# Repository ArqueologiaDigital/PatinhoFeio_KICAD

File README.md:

Para o desenvolvimento desse projeto estou atualmente (Julho de 2025) utilizando o Kicad versão 9.0.2+dfsg-1 instalado a partir do repositório de pacotes do Debian 13.
----

Existe um arquivo patinhofeio.pro na raiz desse repo que referencia os demais sub-projetos de cada placa.

Em JAN/2018 eu encomendei a fabicação das PCBs CDE-3 e CDE-3-debug. Há um relato detalhado em https://forum.fiozera.com.br/t/resgate-historico-do-computador-patinho-feio-usp-1971/58/18

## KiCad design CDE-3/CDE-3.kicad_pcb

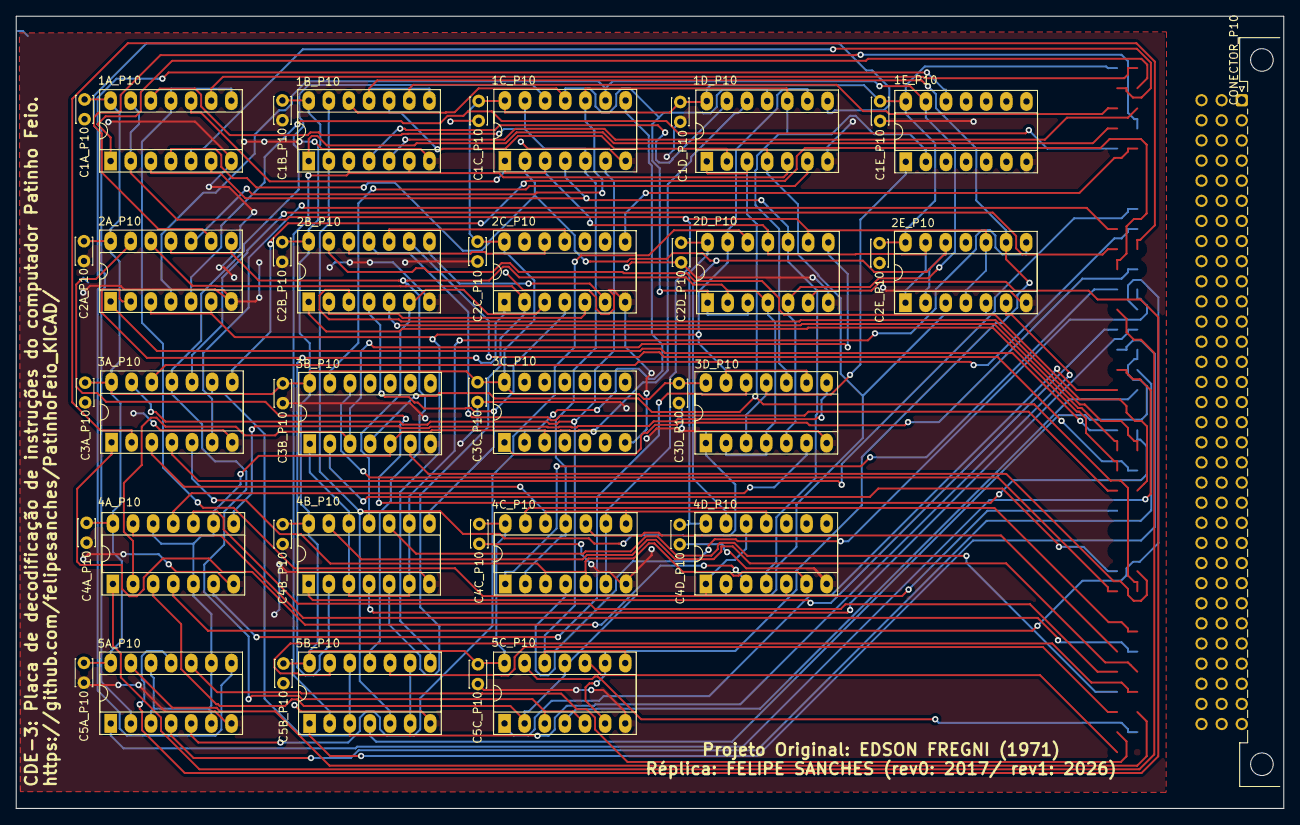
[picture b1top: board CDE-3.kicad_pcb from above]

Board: 2 copper layers, 160.0 x 100.0 mm, 43 parts (0 on the bottom side), 96 nets.

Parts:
1A_P10, 1B_P10, 2A_P10, 2B_P10, 3A_P10, 3B_P10: 74HC04; DIP-14_W7.62mm_Socket_LongPads
1C_P10, 1D_P10, 1E_P10, 2D_P10, 3D_P10: 74LS10; DIP-14_W7.62mm_Socket_LongPads
2C_P10: 74LS30; DIP-14_W7.62mm_Socket_LongPads
2E_P10: 74LS13; DIP-14_W7.62mm_Socket_LongPads
3C_P10, 4A_P10, 4B_P10, 4C_P10, 5A_P10, 5B_P10, 5C_P10: 7402; DIP-14_W7.62mm_Socket_LongPads
4D_P10: 7400; DIP-14_W7.62mm_Socket_LongPads
C1A_P10, C1B_P10, C1C_P10, C1D_P10, C1E_P10, C2A_P10, C2B_P10, C2C_P10, C2D_P10, C2E_P10, C3A_P10, C3B_P10, C3C_P10, C3D_P10, C4A_P10, C4B_P10, C4C_P10, C4D_P10, C5A_P10, C5B_P10, C5C_P10: 0.1uF; C_Disc_D3.4mm_W2.1mm_P2.50mm
CONECTOR_P10: CONN_35X2; DIN41612_C_3x32_Male_Horizontal_THT

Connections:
(+)RI_0: 1A_P10.10, 1C_P10.1, 1C_P10.3, 2D_P10.11, 2E_P10.1, 2E_P10.13
(+)RI_1: 1A_P10.4, 1C_P10.2, 2E_P10.2, 2E_P10.12, 4D_P10.13
(+)RI_2: 1A_P10.12, 1C_P10.5, 1C_P10.13, 4C_P10.2, 4C_P10.11
(+)RI_3: 1B_P10.10, 1D_P10.2, 1D_P10.4, 2E_P10.5, 4A_P10.3, 4D_P10.2, 5C_P10.2, 5C_P10.11
(+)RI_4: 1B_P10.4, 1D_P10.13
(+)RI_5: 1B_P10.12, 1C_P10.11, 1D_P10.11, 2D_P10.1, 2D_P10.3
(+)RI_6: 1C_P10.10, 1D_P10.10, 1E_P10.2, 2A_P10.10, 3D_P10.10
(+)RI_7: 1C_P10.9, 1E_P10.13, 2A_P10.4, 2D_P10.5, 3D_P10.5
+(CAC+SOM): 3A_P10.4, CONECTOR_P10.a20
+(PAN+PAZ): 3A_P10.10, CONECTOR_P10.a16
+(PLI+ARA): 3A_P10.6, CONECTOR_P10.a18
+(SUS+PUG): 3A_P10.12, CONECTOR_P10.a17
+ARA: 4C_P10.4, CONECTOR_P10.a8
+CAC: 4C_P10.13, CONECTOR_P10.b12
+ESP-D: 5A_P10.4, CONECTOR_P10.a32
+IME: 3A_P10.8, CONECTOR_P10.a29
+IMEADD: 5B_P10.1, CONECTOR_P10.c13
+IMENAND: 5B_P10.4, CONECTOR_P10.a7
+IMEXOR: 5B_P10.13, CONECTOR_P10.c7
+INDICE: 3A_P10.2, CONECTOR_P10.a15
+INI: 4A_P10.10, CONECTOR_P10.c10
+MIC: 1D_P10.1, 1D_P10.3, 3B_P10.4, CONECTOR_P10.c4
+MICG1: 4A_P10.1, CONECTOR_P10.a11
+MICG2A: 3B_P10.12, CONECTOR_P10.b26
+MICG2B: 3B_P10.6, CONECTOR_P10.a19
+PAN: 5C_P10.13, CONECTOR_P10.c21
+PAR-D: 5A_P10.13, CONECTOR_P10.b17
+PAZ: 5C_P10.10, CONECTOR_P10.b11
+PER: 5A_P10.1, CONECTOR_P10.c31
+PLI: 4C_P10.1, CONECTOR_P10.b31
+PUG: 5C_P10.4, CONECTOR_P10.a13
+PUL: 4A_P10.4, CONECTOR_P10.a10
+RD_0: 2A_P10.1, CONECTOR_P10.a9
+RD_1: 2A_P10.13, CONECTOR_P10.b14
+RD_2: 2B_P10.5, CONECTOR_P10.a4
+RD_3: 2B_P10.3, CONECTOR_P10.a3
+RD_4: 2B_P10.1, CONECTOR_P10.b25
+RD_5: 2B_P10.9, CONECTOR_P10.c5
+RD_6: 2B_P10.11, CONECTOR_P10.b10
+RD_7: 2B_P10.13, CONECTOR_P10.b6
+RESERVADO: 3C_P10.1, CONECTOR_P10.a28
+RI_0: 1A_P10.9, CONECTOR_P10.a2
+RI_1: 1A_P10.5, CONECTOR_P10.b1
+RI_2: 1A_P10.1, CONECTOR_P10.b2
+RI_3: 1B_P10.9, CONECTOR_P10.c1
+RI_4: 1B_P10.5, CONECTOR_P10.c2
+RI_5: 1B_P10.1, CONECTOR_P10.a25
+RI_6: 2A_P10.9, CONECTOR_P10.b19
+RI_7: 2A_P10.5, CONECTOR_P10.b16
+SAE: 3B_P10.2, CONECTOR_P10.a31
+SAEDE: 4B_P10.4, CONECTOR_P10.b28
+SAEDS: 4B_P10.1, CONECTOR_P10.b32
+SAEFU: 4B_P10.10, CONECTOR_P10.c8
+SAESA: 4B_P10.13, CONECTOR_P10.c9
+SHIFT: 5B_P10.10, CONECTOR_P10.c14
+SOM: 4C_P10.10, CONECTOR_P10.c12
+SUS: 5C_P10.1, CONECTOR_P10.b20
+TRI: 5A_P10.10, CONECTOR_P10.b18
+TRO: 4A_P10.13, CONECTOR_P10.c11
-RDZ: 2C_P10.8, CONECTOR_P10.b15
-RD_0: 2A_P10.2, 2C_P10.1, 4B_P10.2
-RD_1: 2A_P10.12, 2C_P10.2, 4B_P10.5
-RD_2: 2B_P10.6, 2C_P10.3, 4B_P10.11
-RD_3: 2B_P10.4, 2C_P10.4, 4B_P10.8
-RD_4: 2B_P10.2, 2C_P10.5
-RD_5: 2B_P10.8, 2C_P10.6
-RD_6: 2B_P10.10, 2C_P10.11
-RD_7: 2B_P10.12, 2C_P10.12
-RI_0: 1A_P10.8, 1A_P10.11, 4D_P10.1, 4D_P10.5, 4D_P10.12, CONECTOR_P10.b13
-RI_1: 1A_P10.3, 1A_P10.6, 1C_P10.4, 2D_P10.10, 4D_P10.4
-RI_2: 1A_P10.2, 1A_P10.13, 2D_P10.9, 2E_P10.4, 2E_P10.10, 4C_P10.6, 4C_P10.9
-RI_3: 1B_P10.8, 1B_P10.11, 2E_P10.9, 5C_P10.6, 5C_P10.9
-RI_4: 1B_P10.3, 1B_P10.6, 1D_P10.5, 5B_P10.2
-RI_5: 1B_P10.2, 1B_P10.13, 1E_P10.1, 3D_P10.1, 3D_P10.3, 3D_P10.11, 5B_P10.5
-RI_6: 2A_P10.8, 2A_P10.11, 2D_P10.2, 2D_P10.4, 3D_P10.2, 3D_P10.4, 5B_P10.11
-RI_7: 1D_P10.9, 2A_P10.3, 2A_P10.6, 2D_P10.13, 3D_P10.9, 3D_P10.13, 5B_P10.8
GND: 1A_P10.7, 1B_P10.7, 1C_P10.7, 1D_P10.7, 1E_P10.7, 2A_P10.7, 2B_P10.7, 2C_P10.7, 2D_P10.7, 2E_P10.7, 3A_P10.7, 3B_P10.7, 3C_P10.7, 3D_P10.7, 4A_P10.7, 4B_P10.7, 4C_P10.7, 4D_P10.7, 5A_P10.7, 5B_P10.7, 5C_P10.7, C1A_P10.2, C1B_P10.2, C1C_P10.2, C1D_P10.2, C1E_P10.2, C2A_P10.2, C2B_P10.2, C2C_P10.2, C2D_P10.2, C2E_P10.2, C3A_P10.2, C3B_P10.2, C3C_P10.2, C3D_P10.2, C4A_P10.2, C4B_P10.2, C4C_P10.2, C4D_P10.2, C5A_P10.2, C5B_P10.2, C5C_P10.2, CONECTOR_P10.c22
unnamed: 1C_P10.6, 3A_P10.13, 5C_P10.8, 5C_P10.12
unnamed: 1C_P10.8, 3C_P10.2
unnamed: 1C_P10.12, 3A_P10.11, 5C_P10.3, 5C_P10.5
unnamed: 1D_P10.6, 3B_P10.13
unnamed: 1D_P10.8, 5A_P10.8
unnamed: 1D_P10.12, 3B_P10.5, 3C_P10.3, 4A_P10.5, 4A_P10.9, 4A_P10.12, 5A_P10.3, 5A_P10.6, 5A_P10.9, 5A_P10.12
unnamed: 1E_P10.12, 5A_P10.2
unnamed: 2D_P10.6, 5A_P10.11
unnamed: 2D_P10.8, 3B_P10.3, 4A_P10.2
unnamed: 2D_P10.12, 5A_P10.5
unnamed: 2E_P10.6, 3A_P10.9, 5B_P10.3, 5B_P10.6, 5B_P10.9, 5B_P10.12
unnamed: 2E_P10.8, 3B_P10.1, 4B_P10.3, 4B_P10.6, 4B_P10.9, 4B_P10.12
unnamed: 3A_P10.1, 4D_P10.3
unnamed: 3A_P10.3, 4C_P10.8, 4C_P10.12, 4D_P10.11
unnamed: 3A_P10.5, 4C_P10.3, 4C_P10.5, 4D_P10.6
unnamed: 3D_P10.6, 4A_P10.11
unnamed: 3D_P10.8, 4A_P10.8
unnamed: 3D_P10.12, 4A_P10.6
VCC: 1A_P10.14, 1B_P10.14, 1C_P10.14, 1D_P10.14, 1E_P10.14, 2A_P10.14, 2B_P10.14, 2C_P10.14, 2D_P10.14, 2E_P10.14, 3A_P10.14, 3B_P10.14, 3C_P10.14, 3D_P10.14, 4A_P10.14, 4B_P10.14, 4C_P10.14, 4D_P10.14, 5A_P10.14, 5B_P10.14, 5C_P10.14, C1A_P10.1, C1B_P10.1, C1C_P10.1, C1D_P10.1, C1E_P10.1, C2A_P10.1, C2B_P10.1, C2C_P10.1, C2D_P10.1, C2E_P10.1, C3A_P10.1, C3B_P10.1, C3C_P10.1, C3D_P10.1, C4A_P10.1, C4B_P10.1, C4C_P10.1, C4D_P10.1, C5A_P10.1, C5B_P10.1, C5C_P10.1, CONECTOR_P10.a1

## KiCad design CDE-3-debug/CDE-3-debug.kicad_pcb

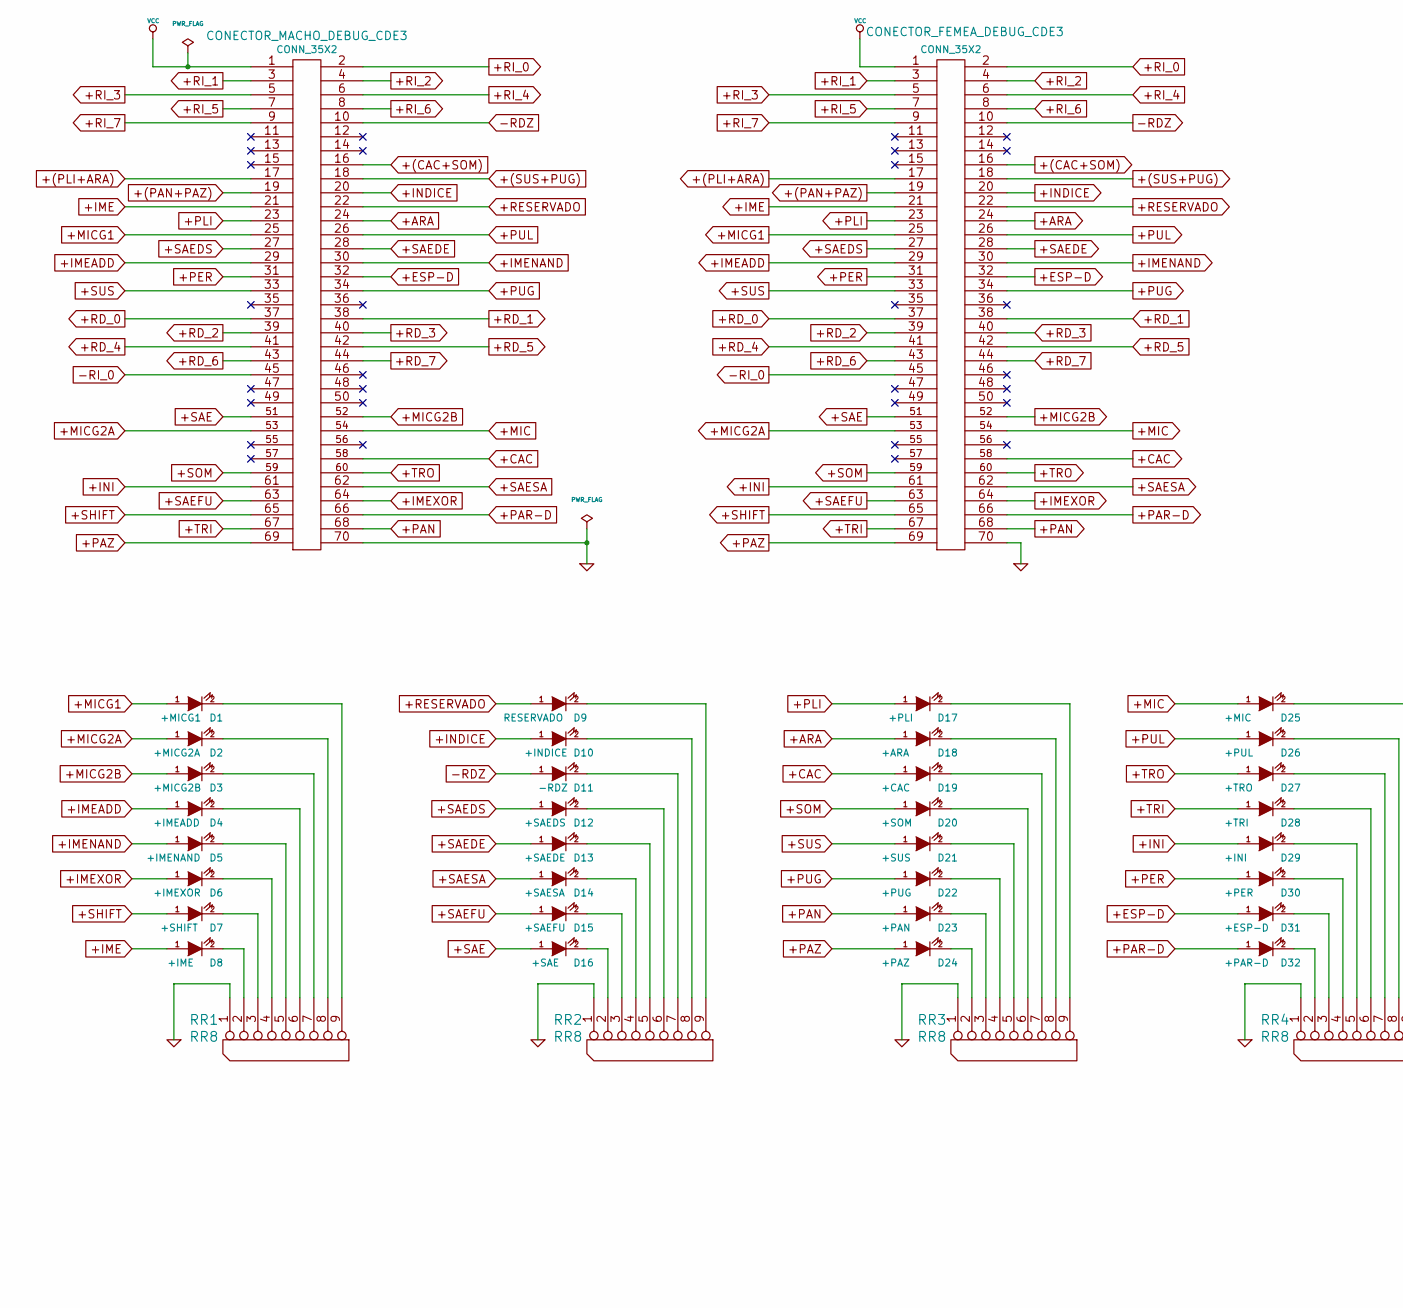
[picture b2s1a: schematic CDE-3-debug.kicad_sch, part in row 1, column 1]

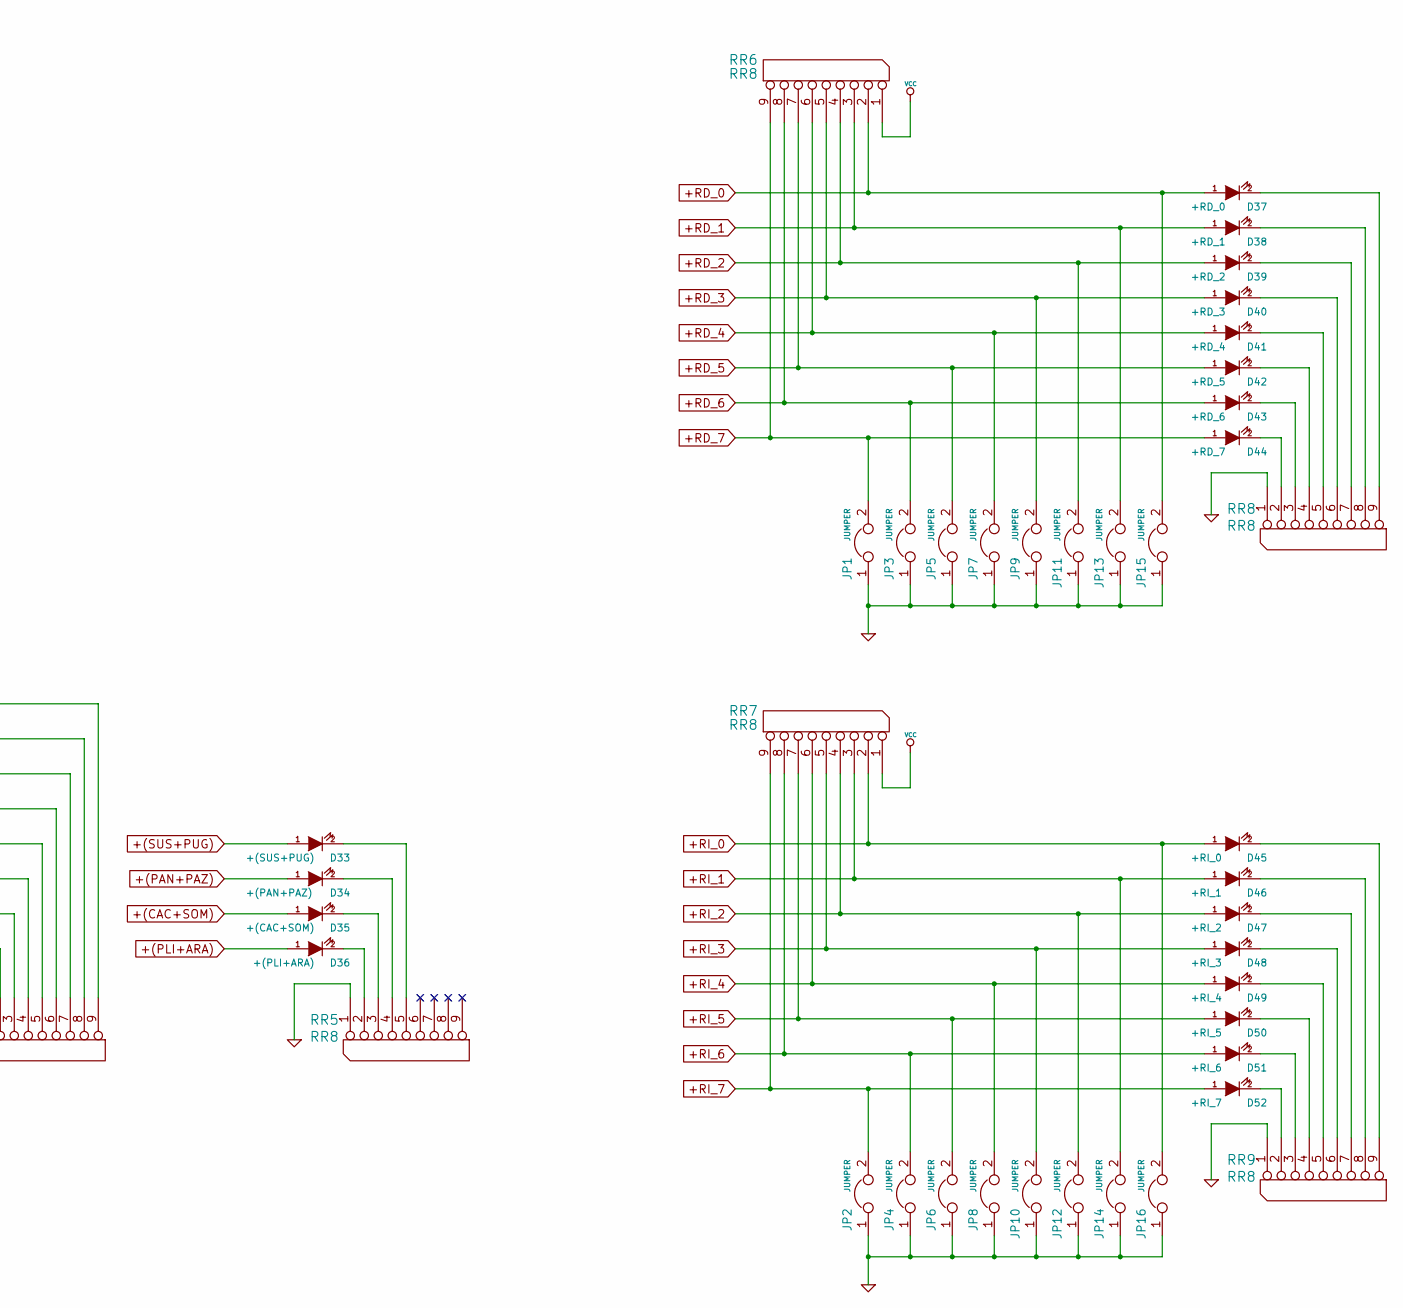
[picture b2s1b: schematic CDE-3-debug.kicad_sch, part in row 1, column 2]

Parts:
CONECTOR_FEMEA_DEBUG_CDE3: CONN_35X2; Pin_Header_Angled_2x35_Pitch2.54mm
CONECTOR_MACHO_DEBUG_CDE3: CONN_35X2; Pin_Header_Angled_2x35_Pitch2.54mm
D1: +MICG1; LED_D3.0mm
D2: +MICG2A; LED_D3.0mm
D3: +MICG2B; LED_D3.0mm
D4: +IMEADD; LED_D3.0mm
D5: +IMENAND; LED_D3.0mm
D6: +IMEXOR; LED_D3.0mm
D7: +SHIFT; LED_D3.0mm
D8: +IME; LED_D3.0mm
D9: RESERVADO; LED_D3.0mm
D10: +INDICE; LED_D3.0mm
D11: -RDZ; LED_D3.0mm
D12: +SAEDS; LED_D3.0mm
D13: +SAEDE; LED_D3.0mm
D14: +SAESA; LED_D3.0mm
D15: +SAEFU; LED_D3.0mm
D16: +SAE; LED_D3.0mm
D17: +PLI; LED_D3.0mm
D18: +ARA; LED_D3.0mm
D19: +CAC; LED_D3.0mm
D20: +SOM; LED_D3.0mm
D21: +SUS; LED_D3.0mm
D22: +PUG; LED_D3.0mm
D23: +PAN; LED_D3.0mm
D24: +PAZ; LED_D3.0mm
D25: +MIC; LED_D3.0mm
D26: +PUL; LED_D3.0mm
D27: +TRO; LED_D3.0mm
D28: +TRI; LED_D3.0mm
D29: +INI; LED_D3.0mm
D30: +PER; LED_D3.0mm
D31: +ESP-D; LED_D3.0mm
D32: +PAR-D; LED_D3.0mm
D33: +(SUS+PUG); LED_D3.0mm
D34: +(PAN+PAZ); LED_D3.0mm
D35: +(CAC+SOM); LED_D3.0mm
D36: +(PLI+ARA); LED_D3.0mm
D37: +RD_0; LED_D3.0mm
D38: +RD_1; LED_D3.0mm
D39: +RD_2; LED_D3.0mm
D40: +RD_3; LED_D3.0mm
D41: +RD_4; LED_D3.0mm
D42: +RD_5; LED_D3.0mm
D43: +RD_6; LED_D3.0mm
D44: +RD_7; LED_D3.0mm
D45: +RI_0; LED_D3.0mm
D46: +RI_1; LED_D3.0mm
D47: +RI_2; LED_D3.0mm
D48: +RI_3; LED_D3.0mm
D49: +RI_4; LED_D3.0mm
D50: +RI_5; LED_D3.0mm
D51: +RI_6; LED_D3.0mm
D52: +RI_7; LED_D3.0mm
JP1, JP2, JP3, JP4, JP5, JP6, JP7, JP8, JP9, JP10, JP11, JP12, JP13, JP14, JP15, JP16: JUMPER; Pin_Header_Straight_1x02_Pitch2.54mm
RR1, RR2, RR3, RR4, RR5, RR6, RR7, RR8, RR9: RR8; R_Array_SIP9

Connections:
+(CAC+SOM): CONECTOR_FEMEA_DEBUG_CDE3.16, CONECTOR_MACHO_DEBUG_CDE3.16, D35.1 (A)
+(PAN+PAZ): CONECTOR_FEMEA_DEBUG_CDE3.19, CONECTOR_MACHO_DEBUG_CDE3.19, D34.1 (A)
+(PLI+ARA): CONECTOR_FEMEA_DEBUG_CDE3.17, CONECTOR_MACHO_DEBUG_CDE3.17, D36.1 (A)
+(SUS+PUG): CONECTOR_FEMEA_DEBUG_CDE3.18, CONECTOR_MACHO_DEBUG_CDE3.18, D33.1 (A)
+ARA: CONECTOR_FEMEA_DEBUG_CDE3.24, CONECTOR_MACHO_DEBUG_CDE3.24, D18.1 (A)
+CAC: CONECTOR_FEMEA_DEBUG_CDE3.58, CONECTOR_MACHO_DEBUG_CDE3.58, D19.1 (A)
+ESP-D: CONECTOR_FEMEA_DEBUG_CDE3.32, CONECTOR_MACHO_DEBUG_CDE3.32, D31.1 (A)
+IME: CONECTOR_FEMEA_DEBUG_CDE3.21, CONECTOR_MACHO_DEBUG_CDE3.21, D8.1 (A)
+IMEADD: CONECTOR_FEMEA_DEBUG_CDE3.29, CONECTOR_MACHO_DEBUG_CDE3.29, D4.1 (A)
+IMENAND: CONECTOR_FEMEA_DEBUG_CDE3.30, CONECTOR_MACHO_DEBUG_CDE3.30, D5.1 (A)
+IMEXOR: CONECTOR_FEMEA_DEBUG_CDE3.64, CONECTOR_MACHO_DEBUG_CDE3.64, D6.1 (A)
+INDICE: CONECTOR_FEMEA_DEBUG_CDE3.20, CONECTOR_MACHO_DEBUG_CDE3.20, D10.1 (A)
+INI: CONECTOR_FEMEA_DEBUG_CDE3.61, CONECTOR_MACHO_DEBUG_CDE3.61, D29.1 (A)
+MIC: CONECTOR_FEMEA_DEBUG_CDE3.54, CONECTOR_MACHO_DEBUG_CDE3.54, D25.1 (A)
+MICG1: CONECTOR_FEMEA_DEBUG_CDE3.25, CONECTOR_MACHO_DEBUG_CDE3.25, D1.1 (A)
+MICG2A: CONECTOR_FEMEA_DEBUG_CDE3.53, CONECTOR_MACHO_DEBUG_CDE3.53, D2.1 (A)
+MICG2B: CONECTOR_FEMEA_DEBUG_CDE3.52, CONECTOR_MACHO_DEBUG_CDE3.52, D3.1 (A)
+PAN: CONECTOR_FEMEA_DEBUG_CDE3.68, CONECTOR_MACHO_DEBUG_CDE3.68, D23.1 (A)
+PAR-D: CONECTOR_FEMEA_DEBUG_CDE3.66, CONECTOR_MACHO_DEBUG_CDE3.66, D32.1 (A)
+PAZ: CONECTOR_FEMEA_DEBUG_CDE3.69, CONECTOR_MACHO_DEBUG_CDE3.69, D24.1 (A)
+PER: CONECTOR_FEMEA_DEBUG_CDE3.31, CONECTOR_MACHO_DEBUG_CDE3.31, D30.1 (A)
+PLI: CONECTOR_FEMEA_DEBUG_CDE3.23, CONECTOR_MACHO_DEBUG_CDE3.23, D17.1 (A)
+PUG: CONECTOR_FEMEA_DEBUG_CDE3.34, CONECTOR_MACHO_DEBUG_CDE3.34, D22.1 (A)
+PUL: CONECTOR_FEMEA_DEBUG_CDE3.26, CONECTOR_MACHO_DEBUG_CDE3.26, D26.1 (A)
+RD_0: CONECTOR_FEMEA_DEBUG_CDE3.37, CONECTOR_MACHO_DEBUG_CDE3.37, D37.1 (A), JP15.2, RR6.2
+RD_1: CONECTOR_FEMEA_DEBUG_CDE3.38, CONECTOR_MACHO_DEBUG_CDE3.38, D38.1 (A), JP13.2, RR6.3
+RD_2: CONECTOR_FEMEA_DEBUG_CDE3.39, CONECTOR_MACHO_DEBUG_CDE3.39, D39.1 (A), JP11.2, RR6.4
+RD_3: CONECTOR_FEMEA_DEBUG_CDE3.40, CONECTOR_MACHO_DEBUG_CDE3.40, D40.1 (A), JP9.2, RR6.5
+RD_4: CONECTOR_FEMEA_DEBUG_CDE3.41, CONECTOR_MACHO_DEBUG_CDE3.41, D41.1 (A), JP7.2, RR6.6
+RD_5: CONECTOR_FEMEA_DEBUG_CDE3.42, CONECTOR_MACHO_DEBUG_CDE3.42, D42.1 (A), JP5.2, RR6.7
+RD_6: CONECTOR_FEMEA_DEBUG_CDE3.43, CONECTOR_MACHO_DEBUG_CDE3.43, D43.1 (A), JP3.2, RR6.8
+RD_7: CONECTOR_FEMEA_DEBUG_CDE3.44, CONECTOR_MACHO_DEBUG_CDE3.44, D44.1 (A), JP1.2, RR6.9
+RESERVADO: CONECTOR_FEMEA_DEBUG_CDE3.22, CONECTOR_MACHO_DEBUG_CDE3.22, D9.1 (A)
+RI_0: CONECTOR_FEMEA_DEBUG_CDE3.2, CONECTOR_MACHO_DEBUG_CDE3.2, D45.1 (A), JP16.2, RR7.2
+RI_1: CONECTOR_FEMEA_DEBUG_CDE3.3, CONECTOR_MACHO_DEBUG_CDE3.3, D46.1 (A), JP14.2, RR7.3
+RI_2: CONECTOR_FEMEA_DEBUG_CDE3.4, CONECTOR_MACHO_DEBUG_CDE3.4, D47.1 (A), JP12.2, RR7.4
+RI_3: CONECTOR_FEMEA_DEBUG_CDE3.5, CONECTOR_MACHO_DEBUG_CDE3.5, D48.1 (A), JP10.2, RR7.5
+RI_4: CONECTOR_FEMEA_DEBUG_CDE3.6, CONECTOR_MACHO_DEBUG_CDE3.6, D49.1 (A), JP8.2, RR7.6
+RI_5: CONECTOR_FEMEA_DEBUG_CDE3.7, CONECTOR_MACHO_DEBUG_CDE3.7, D50.1 (A), JP6.2, RR7.7
+RI_6: CONECTOR_FEMEA_DEBUG_CDE3.8, CONECTOR_MACHO_DEBUG_CDE3.8, D51.1 (A), JP4.2, RR7.8
+RI_7: CONECTOR_FEMEA_DEBUG_CDE3.9, CONECTOR_MACHO_DEBUG_CDE3.9, D52.1 (A), JP2.2, RR7.9
+SAE: CONECTOR_FEMEA_DEBUG_CDE3.51, CONECTOR_MACHO_DEBUG_CDE3.51, D16.1 (A)
+SAEDE: CONECTOR_FEMEA_DEBUG_CDE3.28, CONECTOR_MACHO_DEBUG_CDE3.28, D13.1 (A)
+SAEDS: CONECTOR_FEMEA_DEBUG_CDE3.27, CONECTOR_MACHO_DEBUG_CDE3.27, D12.1 (A)
+SAEFU: CONECTOR_FEMEA_DEBUG_CDE3.63, CONECTOR_MACHO_DEBUG_CDE3.63, D15.1 (A)
+SAESA: CONECTOR_FEMEA_DEBUG_CDE3.62, CONECTOR_MACHO_DEBUG_CDE3.62, D14.1 (A)
+SHIFT: CONECTOR_FEMEA_DEBUG_CDE3.65, CONECTOR_MACHO_DEBUG_CDE3.65, D7.1 (A)
+SOM: CONECTOR_FEMEA_DEBUG_CDE3.59, CONECTOR_MACHO_DEBUG_CDE3.59, D20.1 (A)
+SUS: CONECTOR_FEMEA_DEBUG_CDE3.33, CONECTOR_MACHO_DEBUG_CDE3.33, D21.1 (A)
+TRI: CONECTOR_FEMEA_DEBUG_CDE3.67, CONECTOR_MACHO_DEBUG_CDE3.67, D28.1 (A)
+TRO: CONECTOR_FEMEA_DEBUG_CDE3.60, CONECTOR_MACHO_DEBUG_CDE3.60, D27.1 (A)
-RDZ: CONECTOR_FEMEA_DEBUG_CDE3.10, CONECTOR_MACHO_DEBUG_CDE3.10, D11.1 (A)
-RI_0: CONECTOR_FEMEA_DEBUG_CDE3.45, CONECTOR_MACHO_DEBUG_CDE3.45
GND: CONECTOR_FEMEA_DEBUG_CDE3.70, CONECTOR_MACHO_DEBUG_CDE3.70, JP1.1, JP2.1, JP3.1, JP4.1, JP5.1, JP6.1, JP7.1, JP8.1, JP9.1, JP10.1, JP11.1, JP12.1, JP13.1, JP14.1, JP15.1, JP16.1, RR1.1 (COM), RR2.1 (COM), RR3.1 (COM), RR4.1 (COM), RR5.1 (COM), RR8.1 (COM), RR9.1 (COM)
unnamed: D1.2 (K), RR1.9
unnamed: D2.2 (K), RR1.8
unnamed: D3.2 (K), RR1.7
unnamed: D4.2 (K), RR1.6
unnamed: D5.2 (K), RR1.5
unnamed: D6.2 (K), RR1.4
unnamed: D7.2 (K), RR1.3
unnamed: D8.2 (K), RR1.2
unnamed: D9.2 (K), RR2.9
unnamed: D10.2 (K), RR2.8
unnamed: D11.2 (K), RR2.7
unnamed: D12.2 (K), RR2.6
unnamed: D13.2 (K), RR2.5
unnamed: D14.2 (K), RR2.4
unnamed: D15.2 (K), RR2.3
unnamed: D16.2 (K), RR2.2
unnamed: D17.2 (K), RR3.9
unnamed: D18.2 (K), RR3.8
unnamed: D19.2 (K), RR3.7
unnamed: D20.2 (K), RR3.6
unnamed: D21.2 (K), RR3.5
unnamed: D22.2 (K), RR3.4
unnamed: D23.2 (K), RR3.3
unnamed: D24.2 (K), RR3.2
unnamed: D25.2 (K), RR4.9
unnamed: D26.2 (K), RR4.8
unnamed: D27.2 (K), RR4.7
unnamed: D28.2 (K), RR4.6
unnamed: D29.2 (K), RR4.5
unnamed: D30.2 (K), RR4.4
unnamed: D31.2 (K), RR4.3
unnamed: D32.2 (K), RR4.2
unnamed: D33.2 (K), RR5.5
unnamed: D34.2 (K), RR5.4
unnamed: D35.2 (K), RR5.3
unnamed: D36.2 (K), RR5.2
unnamed: D37.2 (K), RR8.9
unnamed: D38.2 (K), RR8.8
unnamed: D39.2 (K), RR8.7
unnamed: D40.2 (K), RR8.6
unnamed: D41.2 (K), RR8.5
unnamed: D42.2 (K), RR8.4
unnamed: D43.2 (K), RR8.3
unnamed: D44.2 (K), RR8.2
unnamed: D45.2 (K), RR9.9
unnamed: D46.2 (K), RR9.8
unnamed: D47.2 (K), RR9.7
unnamed: D48.2 (K), RR9.6
unnamed: D49.2 (K), RR9.5
unnamed: D50.2 (K), RR9.4
unnamed: D51.2 (K), RR9.3
unnamed: D52.2 (K), RR9.2
VCC: CONECTOR_FEMEA_DEBUG_CDE3.1, CONECTOR_MACHO_DEBUG_CDE3.1, RR6.1 (COM), RR7.1 (COM)

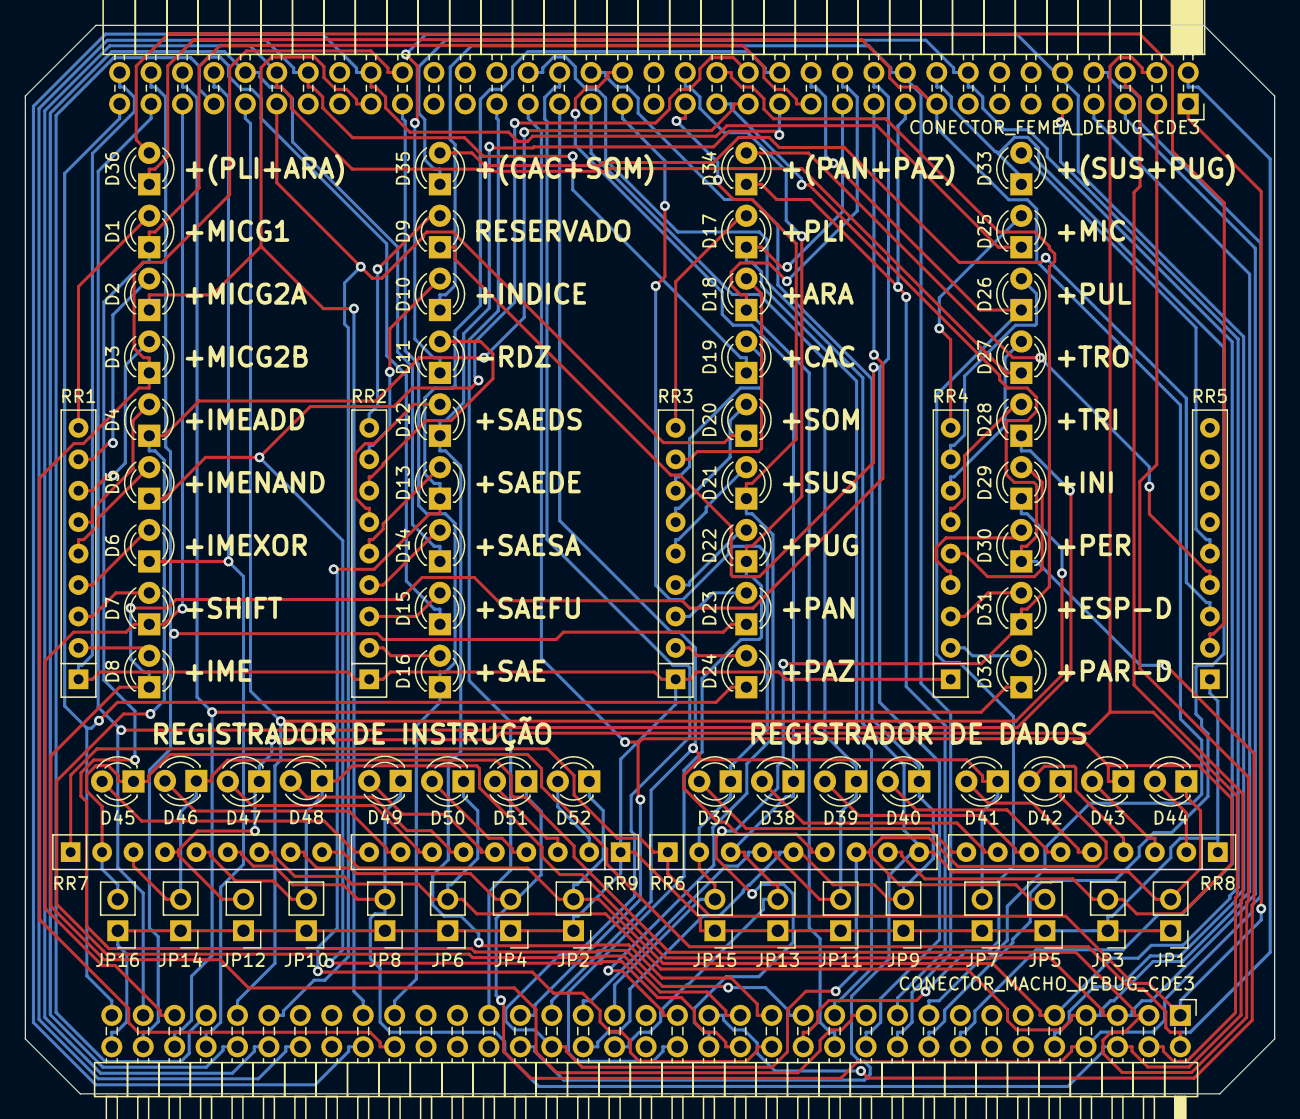
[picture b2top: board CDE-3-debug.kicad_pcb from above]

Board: 2 copper layers, 101.0 x 86.4 mm, 79 parts (0 on the bottom side), 107 nets.

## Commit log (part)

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2016-06-22 inicio do trabalho de transcrição dos esquematicos da tese do Edson Fregni
2016-06-23 mudando o esquema de representação dos nomes dos sinais de input e output
2016-06-25 desenho da prancha do decodificador (prancha X)
2016-06-25 finalizando transcrição inicial do circuito da prancha X
2016-06-25 sufixo de prancha pra deixar o ERC feliz :-(
2016-06-25 usando letras maiusculas nas referencias
2016-06-25 boilerplate para todas as pranchas do esquemático
2016-06-26 wip...
2016-06-28 esquematico da prancha 4 e desenho do componente 7451
2016-06-28 adicionando o nome da prancha 4
2016-07-15 atualizando com Aurelio Heckert
2016-07-31 experimental python script to model a microprogrammed re-implementation of the CPU
    This generates a microcode binary file meant to be stored in an EPROM in order to work as a lookup-table replacement for a large chunk of the original CPU hardwired decoder and control unit.
2016-08-01 minor update to microcode.py
2016-08-01 mais um pedaço de transcrição dos esquematicos
2016-08-01 pequenos ajustes
2016-08-01 trocando pranchas XII <=> XIII
2017-01-02 lista de números dos inputs e outputs da prancha 14
2017-01-04 mais um trecho do esquemático
2017-01-05 mais um pedação do esquemático (prancha XIV)
2017-01-06 transcricao de mais um pouco do esquematico (prancha XIV)
2017-01-06 finalizei a transcrição da prancha XIV! E gerei um PDF dos esquemáticos (incompletos).
2017-01-06 revisei referencias e pinos dos chips de um pedaco incompleto de transcricao da prancha XIII
2017-01-07 mais um pouco...
2017-01-07 script de geração de micro-código (experimental)
2017-01-07 mais um pedaço do circuito (prancha 13)
2017-01-07 finalizei a transcrição da prancha 13
2017-01-07 atualizando o PDF
2017-01-08 mais um pouco de transcrição, agora na prancha 15
2017-01-08 mais um pequeno trecho da prancha 15
2017-01-09 mais um trecho da prancha 15
2017-01-10 finalizada a transcrição da prancha 15! (PDF atualizado)
2017-01-10 redimensionando todas pranchas para tamanho A2
2017-01-10 terminei a transcrição da prancha 9!
2017-01-11 parte do esquemático da prancha 11 (essa prancha é cheia de truquezinhos de projeto e a notação é ambígua e aparentemente contém também diversos error no desenho. Vai ser um desafio interessante desv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
2017-01-11 mais um pouco da prancha 11...
2017-01-13 desenho parcial da prancha 11
2017-01-13 Reorganização geral da folha principal do esquemático adicionando informações com base no texto da tese de mestrado do professor Edson Fregni (Projeto Lógico da Unidade de Controle de Um Minicomputat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
2017-01-16 conector de 70 pinos para a interconexão das placas e término do desenho da prancha 5.
2017-01-16 sinais do conector da prancha 4.
2017-01-16 sinais do conector da prancha 9
2017-01-17 vários trechos de transcrição e, em particular, término do conector dos sinais da prancha 11.
2017-01-17 numerando todas referencias e corrigindo erros de referencias duplas ou pacotes inconsistentes
2017-01-17 wip. acho que preciso separar cada uma das pranchas em um projeto de PCB independente.
2017-01-17 Migrando esquemático da placa CDE-3 (decodificador) para novo projeto.
2017-01-17 Migrando esquemático da prancha 9 (placa CRC-1 - relógio central) para projeto novo.
2017-01-17 Migrando esquemático (incompleto) da prancha 11 (placa CCE-2 - Controle de Estado) para um projeto novo.
2017-01-17 removendo prancha 9 (que já foi migrada para projeto de placa independente)
2017-01-17 removendo prancha 10 (que já foi migrada)
2017-01-17 movendo todos arquivos de pranchas para os diretorios onde teremos novos projetos individuais
2017-01-17 novo projeto: CT1-4 (prancha 12)
2017-01-17 novo projeto: PCB CT2-5 (prancha 13)
2017-01-17 novo projeto: PCB CT3-6 (prancha 14)
2017-01-17 novo projeto: PCB CT4-7 (prancha 15)
2017-01-17 novo projeto: PCB CT5-8 (prancha 16)
2017-01-17 criando novos projetos individuais para todas as outras pranchas que ainda faltavam serem migradas.
2017-01-17 removento arquivos auxiliares que nao sao mais necessarios
2017-01-17 terminando de corrigir todos os error do DRC no esquemático CT5-8
2017-01-18 finalizada transcrição do esquemático PMR-1 (Painel - Mostra Registradores)
2017-01-21 finalizado o desenho da placa PCP-2
2017-01-21 finalizado o desenho do esquematico da placa CT2-5
2017-01-21 terminei a transcrição do esquema da placa CT3-6
2017-01-21 terminei a transcrição do esquema da placa CT4-7
2017-01-23 wip: esquema da placa CT1-4
2017-01-26 ferramenta experimental para gerar o markup de netlist usado pelo MAME a partir de um arquivo de netlist do KICAD
2017-02-03 iniciando o layout da PCB CDE-3
2017-02-03 auto-roteamento da placa CDE-3
2017-02-04 limpando a PCB e preparando os planos de terra e as linhas de corte da borda para re-executar o auto-router. Validei também os critérios de largura e espaçamento de trilhas e diametro de vias para es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
2017-02-04 tentando novamente com uma área d epcb um pouco maior...
2017-02-04 Roteamento automatico com sucesso, placa CDE-3
2017-02-04 CDE-3: adicinando texto descritico à camada de silk superior
2017-02-04 gerbers CDE-3
2017-02-05 schem: CDE-3-debug
2017-02-06 preparando PCB CDE-3-debug
2017-02-06 trocando posição dos conectores macho/femea
2017-02-13 improvements to the CDE-3 and CDE-3-debug boards
2017-02-15 esquematico da placa FIN-8
2018-01-10 Corrigindo erros da rev.A (Eu acabei esquecendo de distribuir o sinal de GND de todos os CIs :-P)
2018-02-15 update schematics symbols on CDE-3 after installing kicad compiled from today's git master source code.
2019-03-03 Bill of Materials da placa CDE-3 que estava solta na minha
    cópia local de trabalho deste repositório, mas acho que vale a pena manter no repo.
2019-03-03 arquivos auxiliares das placas CDE-3 e CDE-3-debug que estavam soltos
    na minha cópia local.
2019-03-03 começando a escrever um README.md
2019-03-03 placa CRC-1: remapping de símbolos após atualização para versao mais nova do KICAD
2019-03-03 plot CRC-1.pdf
2019-03-03 placa CCE-2: remapping de símbolos
2019-03-03 plot CCE-2.pdf
2019-03-03 plot CDE-3.pdf
2019-03-03 placa CDE-3-debug: symbol remap
2019-03-03 plot CDE-3-debug.pdf
2019-03-03 placa CT1-4: symbol remap
2019-03-03 plot CT1-4.pdf
2019-03-03 placa CT2-5: symbol remap
2019-03-03 plot CT2-5.pdf
2019-03-03 placa CT3-6: symbol remap
2019-03-03 plot CT3-6.pdf
2019-03-03 placa CT4-7: symbol remap
2019-03-03 plot CT4-7.pdf
2019-03-03 placa CT5-8: symbol remap
2019-03-03 plot CT5-8.pdf
2019-03-03 placa PCP-2: symbol remap
2019-03-03 plot PCP-2.pdf
2019-03-03 anotando no README a versao do KICAD usada no desenvolvimento deste projeto
2019-03-03 placa PMR-1: symbol remap
2019-03-03 plot PMR-1.pdf
2019-03-03 placa FM1-6: symbol remap
2019-03-03 plot FM1-6.pdf
2019-03-03 placa FCM-7: symbol remap
2019-03-03 plot FCM-7.pdf
2019-03-03 placa FIN-8: symbol remap
2019-03-03 plot FIN-8.pdf
2019-03-03 placa FR1-1: symbol remap
2019-03-03 plot FR1-1.pdf
2019-03-03 placa FS1-3: symbol remap
2019-03-03 plot FS1-3.pdf
2019-03-03 placa FAC-5: symbol remap
2019-03-03 plot FAC-5.pdf
2023-09-12 create: board fac-5
2023-09-13 Esquemáticos para a placa FAC-5
2023-09-13 create: unidade aritimetica
2023-09-13 Criando prancha II - FS1-3 [Unidade Aritimetica]
2025-07-24 left-over changes from my local checkout of the repo
2025-07-24 more files that were left over in my local copy
2025-07-24 "rescuing" symbols and updating schematics files.
    I am now using KICAD version 9.0.2+dfsg-1 installed as a package from Debian 13.
2025-07-24 I believe I can now delete the old version of the schematics files (*.sch)
    Because now we'll use the new format (*.kicad_sch)
2025-07-24 fix references to schematics from the main schem
2025-07-25 fix main schematics sheet and its hierarchical references to the other ones
2025-07-28 remove FAC-5 sch boilerplate
2025-07-28 Convert FAC-5 schematics to new file format
2025-07-28 remove FS1-3 sch boilerplate
2025-07-28 Convert FS1-3 schematics to new file format
2025-07-28 remove auto-generated backup files from version control
2025-07-28 Atualizando README
2025-07-28 update PDF
2025-07-28 ignore autosave files
2025-07-31 initial work on schematics for a backplane to which all boards will be attached.
2025-08-04 wip: backplane connectors
2025-08-04 plot schematics to PDF
2026-06-29 first review and many fixes to FS1-3 board
2026-06-29 I've started modifying the CDE-3 board to use DIN-41612 connectors. This is still wip! I'll get back to it once I receive some sample parts by mail.
2026-06-29 These are updated files after I loaded the project on a new version of KICAD
2026-06-29 I believe that this is an outdated file
2026-06-29 PDF export
2026-06-29 add connectors for FS1_3 and FS2_4 to the backplane
2026-06-29 adding references to a couple NOT gates that are not annotated in the original schematics.
2026-06-29 FS1-3 + FS2-4
2026-06-30 wip: preparing to draw all PCBs
2026-06-30 FR1/FR2 + FS1/FS2
2026-06-30 backplane
